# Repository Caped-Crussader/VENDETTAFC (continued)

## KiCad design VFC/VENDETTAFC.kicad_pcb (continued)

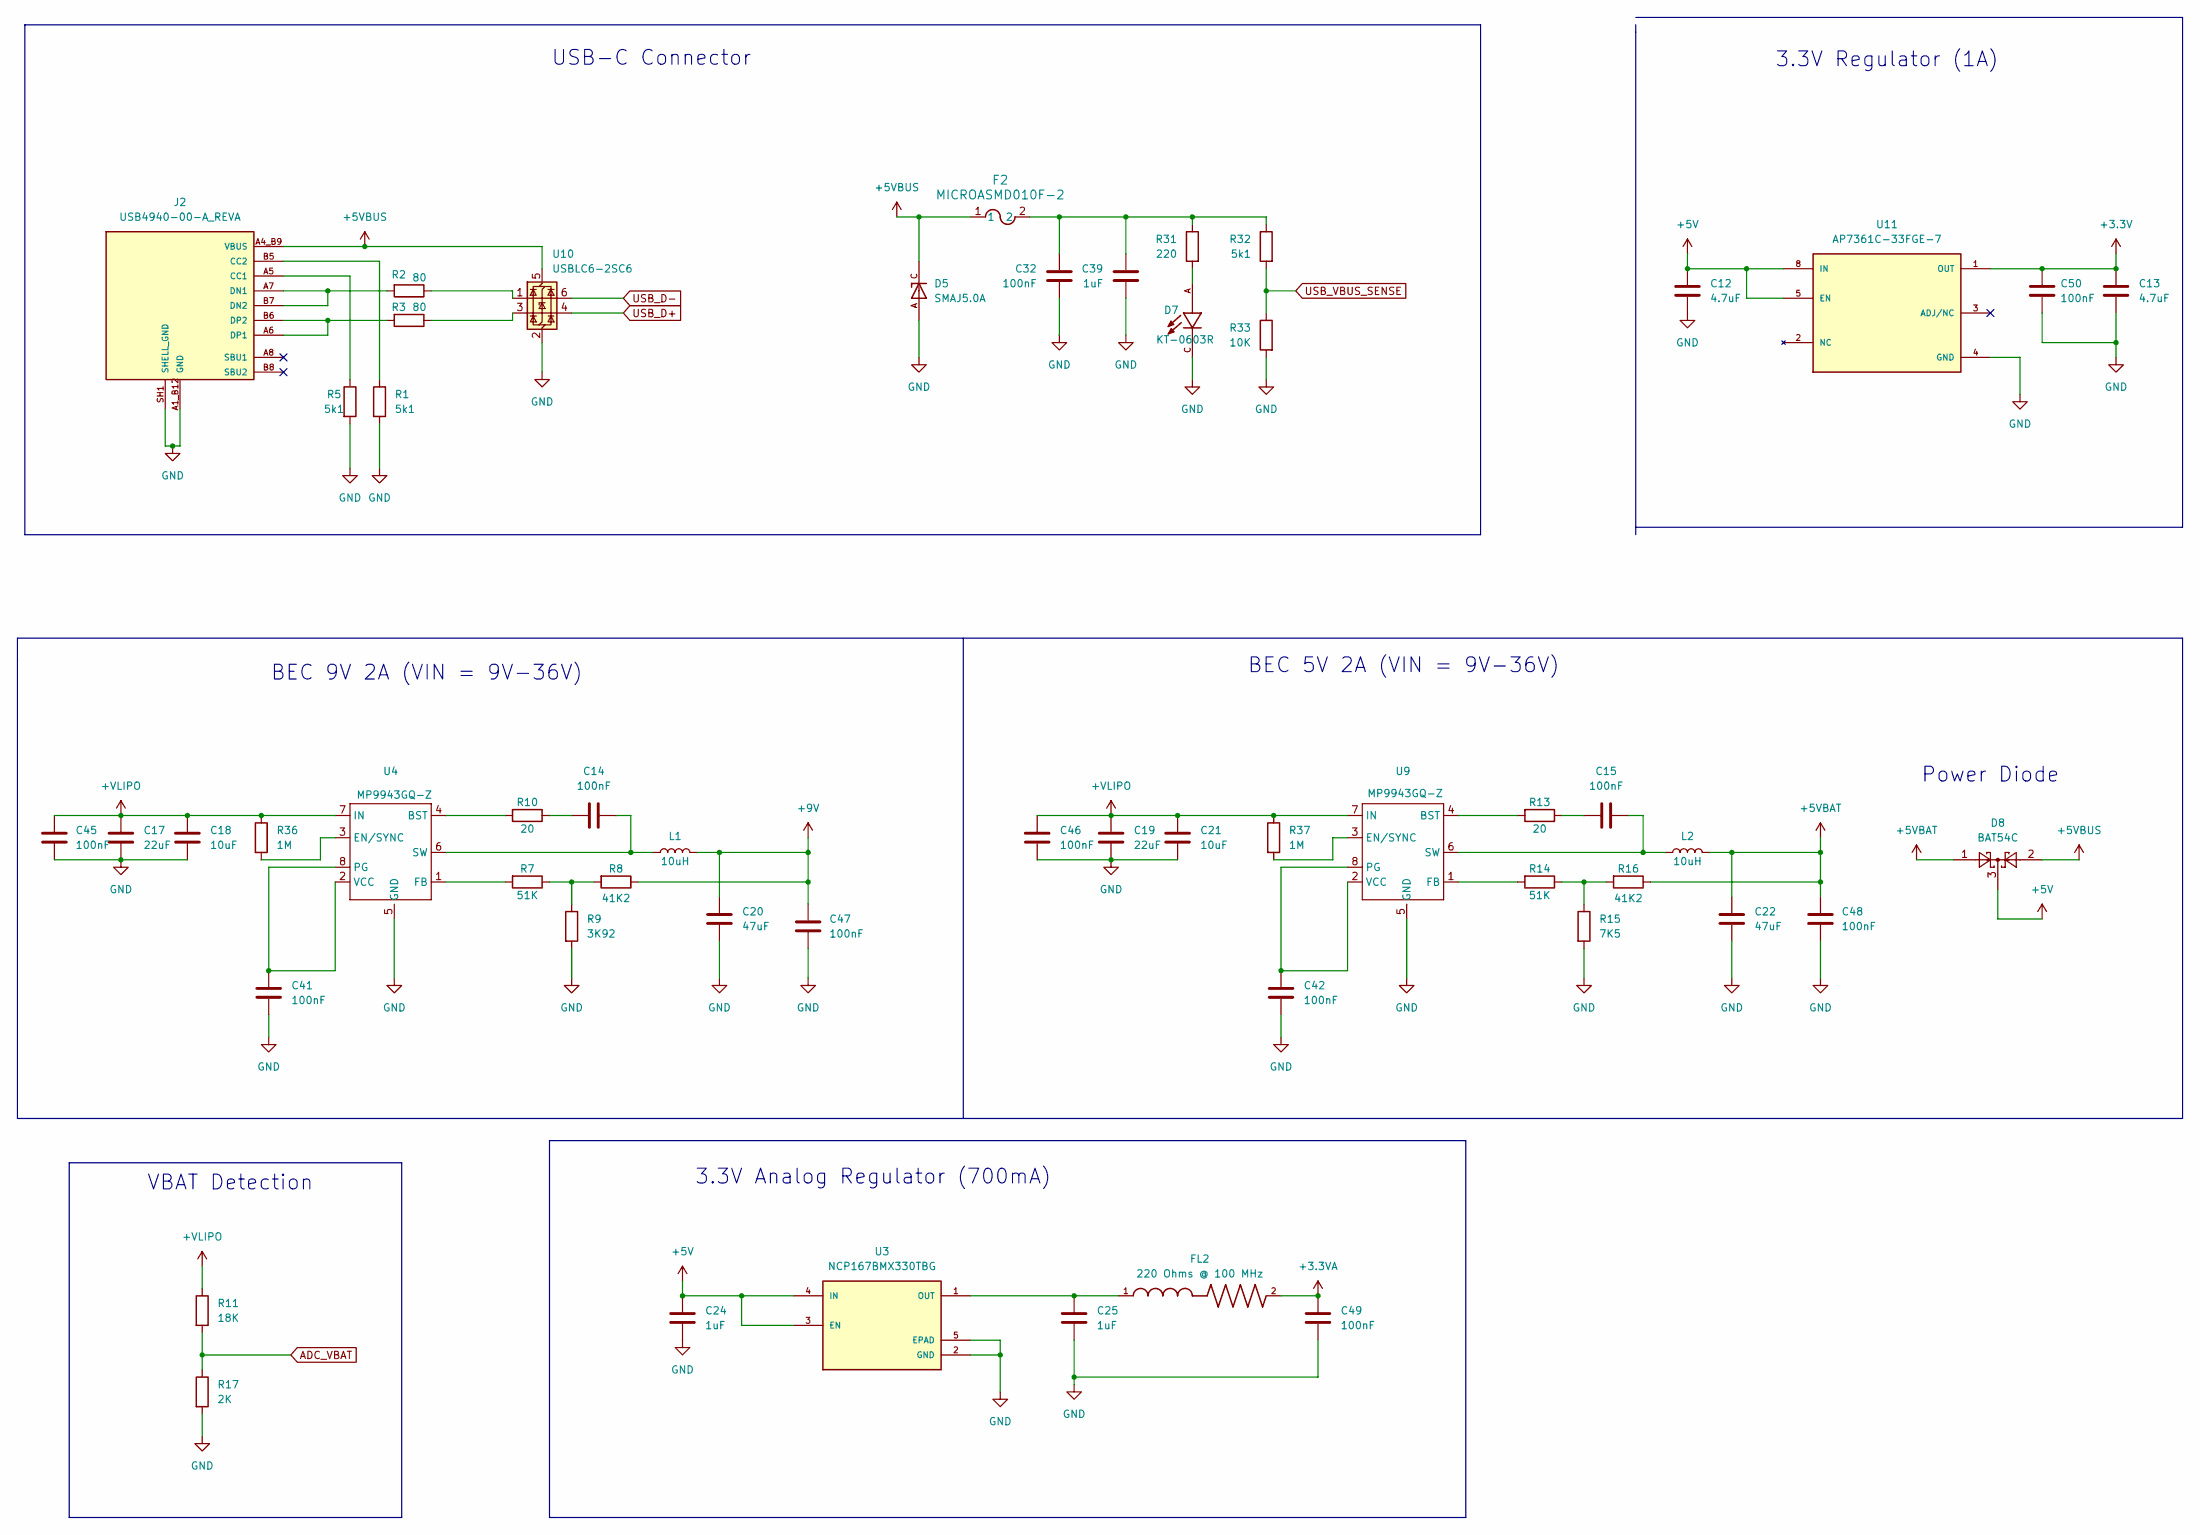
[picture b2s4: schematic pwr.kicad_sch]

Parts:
C12, C13: 4.7uF; C_0603_1608Metric; MANUFACTURER PART NUMBER CL10A475KO8NNNC; LCSC C19666
C14, C15, C32, C41, C42, C45, C46, C47, C48, C49, C50: 100nF; C_0402_1005Metric; MANUFACTURER PART NUMBER CL05A104KA5NNNC; LCSC C100072
C17, C19: 22uF; C_0805_2012Metric; MANUFACTURER PART NUMBER HGC0805R5226M350NSLJ; LCSC C22367832
C18, C21: 10uF; C_0805_2012Metric; MANUFACTURER PART NUMBER CL21A106KBYQNNE; LCSC C2932476
C20, C22: 47uF; C_0805_2012Metric; MANUFACTURER PART NUMBER CL21A476MPYNNWE; LCSC C5596752
C24, C25, C39: 1uF; C_0402_1005Metric; MANUFACTURER PART NUMBER CL05A105KO5NNNC; LCSC C29266
D5: SMAJ5.0A; DIOM4325X250N; PARTREV S2102; LCSC C83329
D7: KT-0603R; LED_KT-0603R; PARTREV 2013/01/24; LCSC C2286
D8: BAT54C; SOT-23; MANUFACTURER PART NUMBER BAT54CLT1G; LCSC C14308
F2: MICROASMD010F-2; FUSE_MICROASMD010F_LTF; MANUFACTURER PART NUMBER MICROSMD010F-2; LCSC C2649903
FL2: 220 Ohms @ 100 MHz; L_0402_1005Metric; MANUFACTURER PART NUMBER BLM15BB221SN1D; LCSC C85818
J2: USB4940-00-A_REVA; GCT_USB4940-00-A_REVA; PARTREV A; LCSC C54829818
L1, L2: 10uH; L_Changjiang_FTC404020S; MANUFACTURER PART NUMBER GXTC0420-100-MT; LCSC C53198553
R1, R5, R32: 5k1; R_0402_1005Metric; MANUFACTURER PART NUMBER RC0402FR-075K1L; LCSC C105872
R2, R3: 80; R_0402_1005Metric; MANUFACTURER PART NUMBER RC0402FR-0780R6L; LCSC C185392
R7, R14: 51K; R_0402_1005Metric; MANUFACTURER PART NUMBER RC0402FR-0751KL; LCSC C107229
R8, R16: 41K2; R_0402_1005Metric; MANUFACTURER PART NUMBER CRCW040241K2FKED; LCSC C844310
R9: 3K92; R_0402_1005Metric; MANUFACTURER PART NUMBER RC0402FR-073K9L; LCSC C131467
R10, R13: 20; R_0402_1005Metric; MANUFACTURER PART NUMBER RC0402FR-0720RL; LCSC C138031
R11: 18K; R_0402_1005Metric; MANUFACTURER PART NUMBER 0402WGF1802TCE; LCSC C25762
R15: 7K5; R_0402_1005Metric; MANUFACTURER PART NUMBER 0402WGF7501TCE; LCSC C25918
R17: 2K; R_0402_1005Metric; MANUFACTURER PART NUMBER RC0402FR-072KL; LCSC C60488
R31: 220; R_0402_1005Metric; MANUFACTURER PART NUMBER RC0402FR-07220RL; LCSC C112291
R33: 10K; R_0402_1005Metric; MANUFACTURER PART NUMBER RC0402JR-0710KL; LCSC C60489
R36, R37: 1M; R_0402_1005Metric; MANUFACTURER PART NUMBER RC0402JR-071ML; LCSC C93949
U3: NCP167BMX330TBG; VREG_NCP167BMX330TBG; PARTREV 5; LCSC C892227
U4, U9: MP9943GQ-Z; QFN-8_MP9943_MNP; MANUFACTURER PART NUMBER MP9943GQ-Z; LCSC Mouser No: 946-MP9943GQ-Z
U10: USBLC6-2SC6; SOT-23-6; MANUFACTURER PART NUMBER USBLC6-2SC6; LCSC C7519
U11: AP7361C-33FGE-7; SON65P300X300X63-9N; PARTREV 5 - 2; LCSC C151007

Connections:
+3.3V: C13.1, C50.1, U11.1 (OUT); also elsewhere on the board
+3.3VA: C49.1, FL2.2; also elsewhere on the board
+5V: C12.1, C24.1, D8.3, U3.3 (EN), U3.4 (IN), U11.5 (EN), U11.8 (IN); also elsewhere on the board
+5VBAT: C22.1, C48.1, D8.1, L2.2, R16.1
+5VBUS: D5.C, D8.2, F2.1, J2.A4_B9 (VBUS), J2.B4_A9 (VBUS), U10.5 (VBUS)
+9V: C20.1, C47.1, L1.2, R8.1; also elsewhere on the board
+VLIPO: C17.1, C18.1, C19.1, C21.1, C45.1, C46.1, R11.1, R36.1, R37.1, U4.7 (IN), U9.7 (IN); also elsewhere on the board
ADC_VBAT: R11.2, R17.1; also elsewhere on the board
GND: C12.2, C13.2, C17.2, C18.2, C19.2, C20.2, C21.2, C22.2, C24.2, C25.2, C32.2, C39.2, C41.2, C42.2, C45.2, C46.2, C47.2, C48.2, C49.2, C50.2, D5.A, D7.C, J2.A1_B12 (GND), J2.B1_A12 (GND), J2.SH1 (SHELL_GND), J2.SH2 (SHELL_GND), J2.SH3 (SHELL_GND), J2.SH4 (SHELL_GND), R1.2, R5.2, R9.2, R15.2, R17.2, R33.2, U3.2 (GND), U3.5 (EPAD), U4.5 (GND), U9.5 (GND), U10.2 (GND), U11.4 (GND), U11.9 (GND); also elsewhere on the board
unnamed: C14.2, R10.1
unnamed: C15.2, R13.1
unnamed: C32.1, C39.1, F2.2, R31.1, R32.1
unnamed: D7.A, R31.2
unnamed: J2.A5 (CC1), R5.1
unnamed: J2.B5 (CC2), R1.1
unnamed: J2.A7 (DN1), J2.B7 (DN2), R2.2
unnamed: J2.A6 (DP1), J2.B6 (DP2), R3.2
unnamed: R2.1, U10.1 (I/O1)
unnamed: R3.1, U10.3 (I/O2)
unnamed: R7.1, R8.2, R9.1
unnamed: R14.1, R15.1, R16.2
unnamed: C25.1, FL2.1, U3.1 (OUT)
unnamed: R10.2, U4.4 (BST)
unnamed: R36.2, U4.3 (EN/SYNC)
unnamed: R7.2, U4.1 (FB)
unnamed: C41.1, U4.2 (VCC), U4.8 (PG)
unnamed: C14.1, L1.1, U4.6 (SW)
unnamed: R13.2, U9.4 (BST)
unnamed: R37.2, U9.3 (EN/SYNC)
unnamed: R14.2, U9.1 (FB)
unnamed: C42.1, U9.2 (VCC), U9.8 (PG)
unnamed: C15.1, L2.1, U9.6 (SW)
USB_D+: U10.4 (I/O2); also elsewhere on the board
USB_D-: U10.6 (I/O1); also elsewhere on the board
USB_VBUS_SENSE: R32.2, R33.1; also elsewhere on the board

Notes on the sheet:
USB-C Connector
3.3V Analog Regulator (700mA)
VBAT Detection
BEC 5V 2A (VIN = 9V-36V)
BEC 9V 2A (VIN = 9V-36V)
Power Diode
3.3V Regulator (1A)

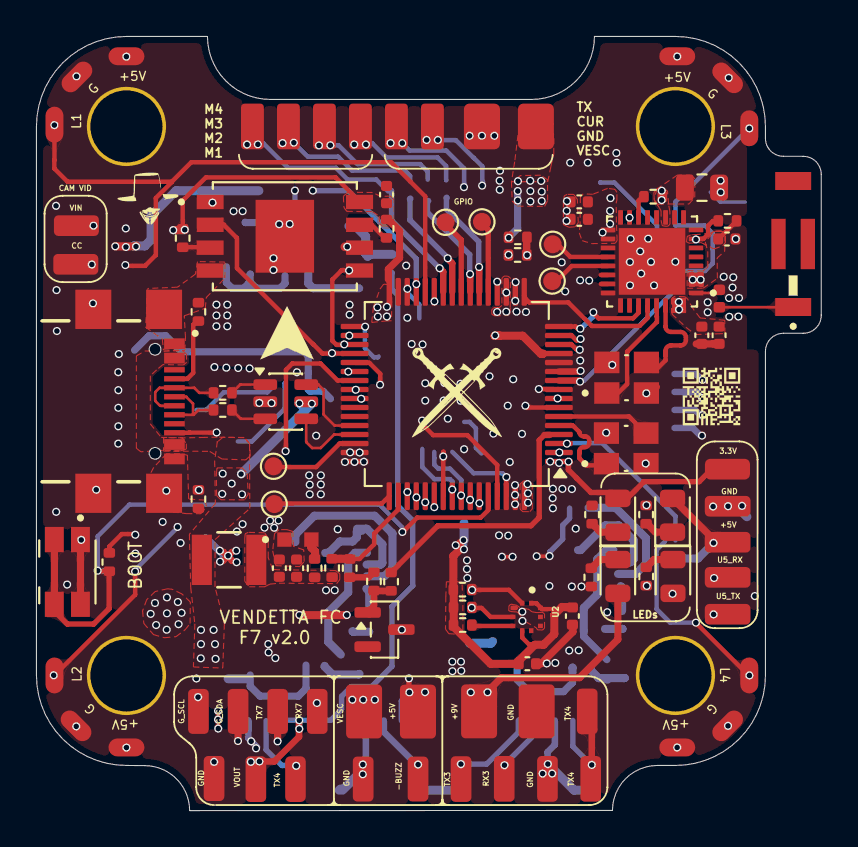
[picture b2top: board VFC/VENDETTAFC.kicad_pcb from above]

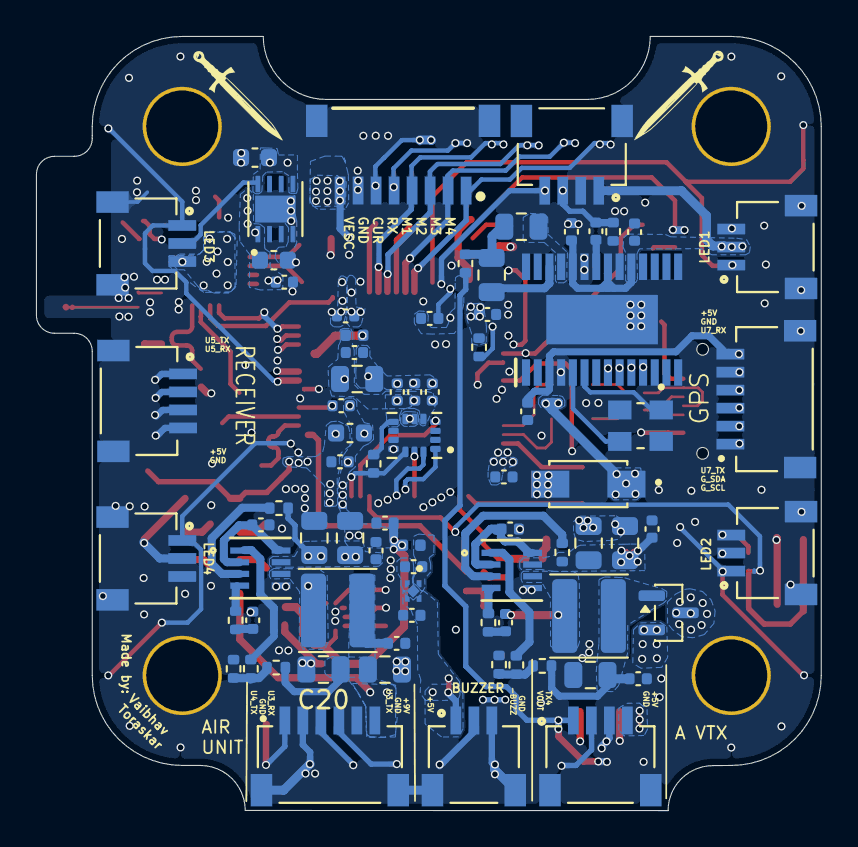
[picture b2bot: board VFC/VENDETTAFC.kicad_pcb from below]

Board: 6 copper layers, 43.6 x 43.0 mm, 180 parts (77 on the bottom side), 107 nets.

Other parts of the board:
TP36#2: TestPoint; TestPoint_Pad_1.0x1.0mm

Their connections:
GND: TP36#2.1 (1_1); also elsewhere on the board

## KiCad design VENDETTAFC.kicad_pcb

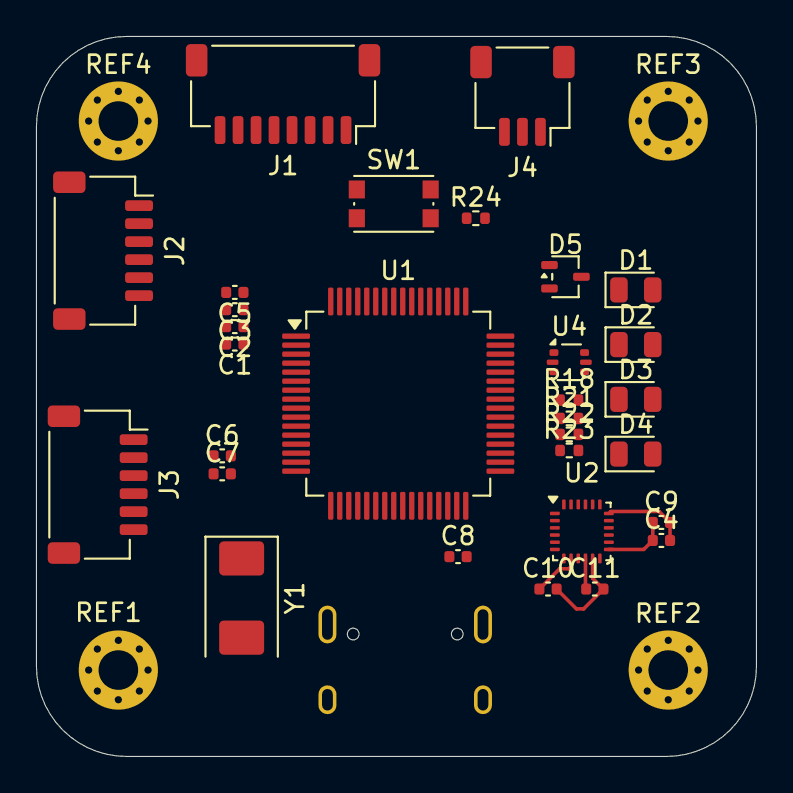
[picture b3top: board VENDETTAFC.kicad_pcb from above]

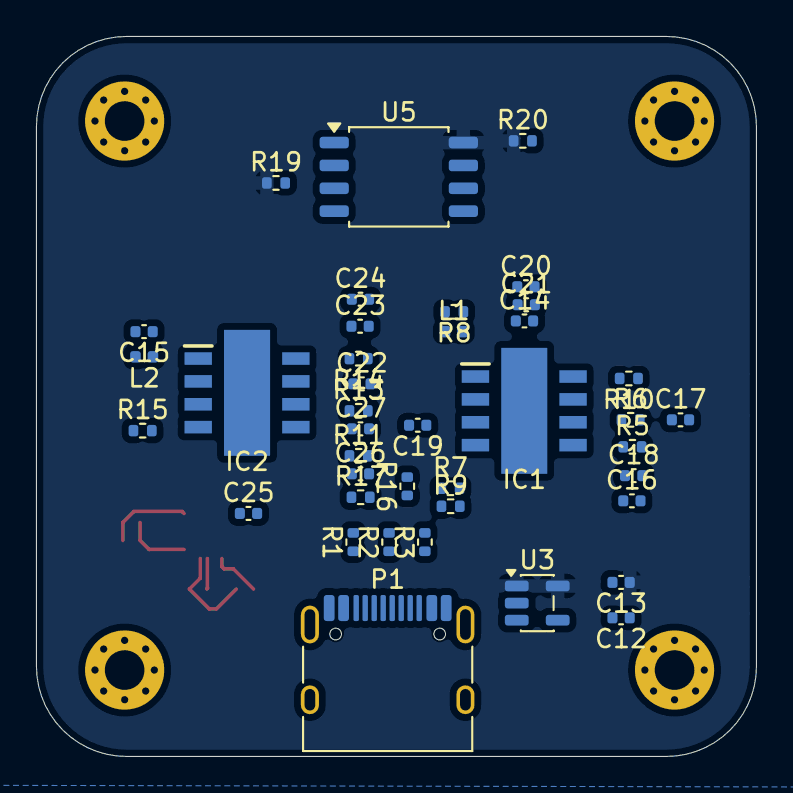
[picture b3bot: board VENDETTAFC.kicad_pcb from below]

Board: 6 copper layers, 40.0 x 40.0 mm, 74 parts (40 on the bottom side), 61 nets.

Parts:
C1, C2, C3, C4, C6, C14, C15: 100nF; C_0402_1005Metric
C5: 4.7uF; C_0402_1005Metric
C7, C18, C24: 1uF; C_0402_1005Metric
C8: 2.2uf; C_0402_1005Metric
C9: 2.2uF; C_0402_1005Metric
C10: 10nF; C_0402_1005Metric
C11: 420pF; C_0402_1005Metric
C12, C13: 1nF; C_0402_1005Metric
C16, C17, C22, C23: 10uF; C_0402_1005Metric
C19, C25: 220pF; C_0402_1005Metric
C20, C21, C26, C27: 22uF; C_0402_1005Metric
D1: LED2; LED_0805_2012Metric
D2: LED3; LED_0805_2012Metric
D3: LED4; LED_0805_2012Metric
D4: LED1; LED_0805_2012Metric
D5: BAT54CW; SOT-323_SC-70
IC1, IC2: MP1584EN-LF-Z; SOIC127P600X170-9N
J1: Conn_01x08_Socket; JST_SH_SM08B-SRSS-TB_1x08-1MP_P1.00mm_Horizontal
J2, J3: Conn_01x06_Socket; JST_SH_SM06B-SRSS-TB_1x06-1MP_P1.00mm_Horizontal
J4: Conn_01x03_Socket; JST_SH_SM03B-SRSS-TB_1x03-1MP_P1.00mm_Horizontal
L1, L2: 10uH; L_0402_1005Metric
P1: USB_C_Plug_USB2.0; USB_C_Receptacle_HRO_TYPE-C-31-M-12
R1: 5k1; R_0402_1005Metric
R2, R3: 80; R_0402_1005Metric
R5, R11: 68K1; R_0402_1005Metric
R6, R13: 200K; R_0402_1005Metric
R7, R15: 51K; R_0402_1005Metric
R8, R17: 41K2; R_0402_1005Metric
R9: 3K92; R_0402_1005Metric
R10, R14: 20; R_0402_1005Metric
R16: 7K5; R_0402_1005Metric
R18: 47; R_0402_1005Metric
R19, R20, R24: 10K; R_0402_1005Metric
R21: 220; R_0402_1005Metric
R22: 1K; R_0402_1005Metric
R23: 75; R_0402_1005Metric
REF1, REF2, REF3, REF4: MountingHole_2.2mm_M2_Pad_Via
SW1: SW_Push; SW_Push_1P1T_NO_CK_KMR2
U1: STM32F722RETx; LQFP-64_10x10mm_P0.5mm
U2: ICM-20948; InvenSense_QFN-24_3x3mm_P0.4mm
U3: RT9701; SOT-23-5
U4: USBLC6-2P6; SOT-666
U5: W25Q128JVS; SOIC-8_5.3x5.3mm_P1.27mm
Y1: Crystal; Crystal_SMD_0603-2Pin_6.0x3.5mm

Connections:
+3.3V: C1.1, C2.1, C3.1, C4.1, C5.1, C6.1, C7.1, C9.1, C10.1, C13.1, D1.2 (A), R19.1, R20.1, SW1.1, U1.1 (VBAT), U1.13 (VDDA), U1.19 (VDD), U1.32 (VDD), U1.48 (VDD), U1.64 (VDD), U2.8 (VDDIO), U2.13 (VDD), U3.1 (VOUT), U3.5 (VOUT), U5.8 (VCC)
+5V: C12.1, D2.2 (A), J3.4, U3.3 (VIN), U3.4 (VIN/EN)
+5VBAT: C26.1, C27.1, D5.1, L2.2, R17.1
+9V: C20.1, C21.1, D3.2 (A), J2.6, J4.3, L1.2, R8.1
+VLIPO: C16.1, C17.1, C18.1, C22.1, C23.1, C24.1, IC1.7 (VIN), IC2.7 (VIN), J1.7
/ADC_CUR: J1.1, U1.9 (PC1)
/BOOT0: R24.1, SW1.2, U1.60 (BOOT0)
/FLASH_CS: U1.41 (PA8), U5.1 (~CS)
/GYRO_CS: U1.20 (PA4), U2.22 (~CS)
/GYRO_INT: U1.25 (PB0), U2.12 (INT1)
/HSE_IN: U1.5 (PH0), Y1.1
/HSE_OUT: U1.6 (PH1), Y1.2
/LED0: D4.2 (A), U1.46 (PA13)
/MOTOR1: J1.6, U1.56 (PB4)
/MOTOR2: J1.5, U1.55 (PB3)
/MOTOR3: J1.4, U1.38 (PC7)
/MOTOR4: J1.3, U1.39 (PC8)
/SPI1_SCK: U1.21 (PA5), U2.23 (SCL/SCLK)
/SPI1_SDI: U1.23 (PA7), U2.24 (SDA/SDI)
/SPI1_SDO: U1.22 (PA6), U2.9 (SDO/AD0)
/SPI2_SCK: U1.34 (PB13), U5.6 (CLK)
/SPI2_SDI: U1.36 (PB15), U5.5 (DI/IO_{0})
/SPI2_SDO: U1.35 (PB14), U5.2 (DO/IO_{1})
/UART1_RX: J2.1, U1.59 (PB7)
/UART2_RX: J2.3, U1.17 (PA3)
/UART2_TX: J2.4, J3.2, U1.16 (PA2)
/UART3_RX: J1.2, U1.52 (PC11)
/USB_CON_D+: R3.1, U4.1 (I/O1)
/USB_CON_D-: R2.1, U4.3 (I/O2)
/USB_D+: U1.44 (PA11), U4.6 (I/O1)
/USB_D-: U1.45 (PA12), U4.4 (I/O2)
/VIDEO: J3.1, J4.1
GND: C1.2, C2.2, C3.2, C4.2, C5.2, C6.2, C7.2, C8.2, C9.2, C10.2, C11.2, C12.2, C13.2, C16.2, C17.2, C18.2, C20.2, C21.2, C22.2, C23.2, C24.2, C26.2, C27.2, D5.3, IC1.5 (GND), IC1.9 (EP), IC2.5 (GND), IC2.9 (EP), J1.8, J2.2, J2.5, J3.3, J3.5, J3.6, J4.2, P1.A1 (GND), P1.A12 (GND), P1.B1 (GND), P1.B12 (GND), P1.SH (SHIELD), R1.2, R5.2, R6.2, R9.2, R11.2, R13.2, R16.2, R18.2, R21.2, R22.2, R23.2, R24.2, U1.12 (VSSA), U1.18 (VSS), U1.31 (VSS), U1.47 (VSS), U1.63 (VSS), U2.11 (FSYNC), U2.18 (GND), U2.20 (GND), U3.2 (GND), U4.2 (GND), U5.4 (GND)
unnamed: C14.2, R10.1
unnamed: C15.2, R14.1
unnamed: C19.2, R5.1
unnamed: C25.2, R11.1
unnamed: D1.1 (K), R18.1
unnamed: D2.1 (K), R21.1
unnamed: D3.1 (K), R22.1
unnamed: D4.1 (K), R23.1
unnamed: IC1.8 (BST), R10.2
unnamed: C19.1, IC1.3 (COMP)
unnamed: IC1.4 (FB), R7.2
unnamed: IC1.6 (FREQ), R6.1
unnamed: C14.1, IC1.1 (SW), L1.1
unnamed: IC2.8 (BST), R14.2
unnamed: C25.1, IC2.3 (COMP)
unnamed: IC2.4 (FB), R15.2
unnamed: IC2.6 (FREQ), R13.1
unnamed: C15.1, IC2.1 (SW), L2.1
unnamed: P1.A5 (CC), R1.1
unnamed: P1.A6 (D+), R3.2
unnamed: P1.A7 (D-), R2.2
unnamed: R7.1, R8.2, R9.1
unnamed: R15.1, R16.1, R17.2
unnamed: C8.1, U1.30 (VCAP_1)
unnamed: C11.1, U2.10 (REGOUT)
unnamed: R20.2, U5.7 (~HOLD/~RESET/IO_{3})
unnamed: R19.2, U5.3 (~WP/IO_{2})
VBUS: D5.2, P1.A4 (VBUS), P1.A9 (VBUS), P1.B4 (VBUS), P1.B5 (VCONN), P1.B9 (VBUS), U4.5 (VBUS)

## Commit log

2026-04-30 added VESC (revision_1)
2026-04-30 Update README.md for VESC
2026-05-02 Revision_2 of VESC
2026-05-02 Added BOM, gerbers
2026-05-06 Updated VFC schematic
2026-05-08 VFC PCB components placements complete
2026-05-09 VFC PCB traces update
2026-05-10 Revision_1 of VFC complete
2026-05-10 Added LICENSE
2026-05-12 LICENSE
2026-05-22 Added fabrication files
2026-05-23 Routing improvements
2026-05-28 Added telemetery feature for ESC
2026-05-29 VESC Revision 2.0
2026-05-30 VFC Revision 2.0
2026-06-01 Rev 2.0 fabrication documentation
